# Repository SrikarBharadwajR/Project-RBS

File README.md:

# Project-RBS
A fully autonomous rubik's cube solving robot

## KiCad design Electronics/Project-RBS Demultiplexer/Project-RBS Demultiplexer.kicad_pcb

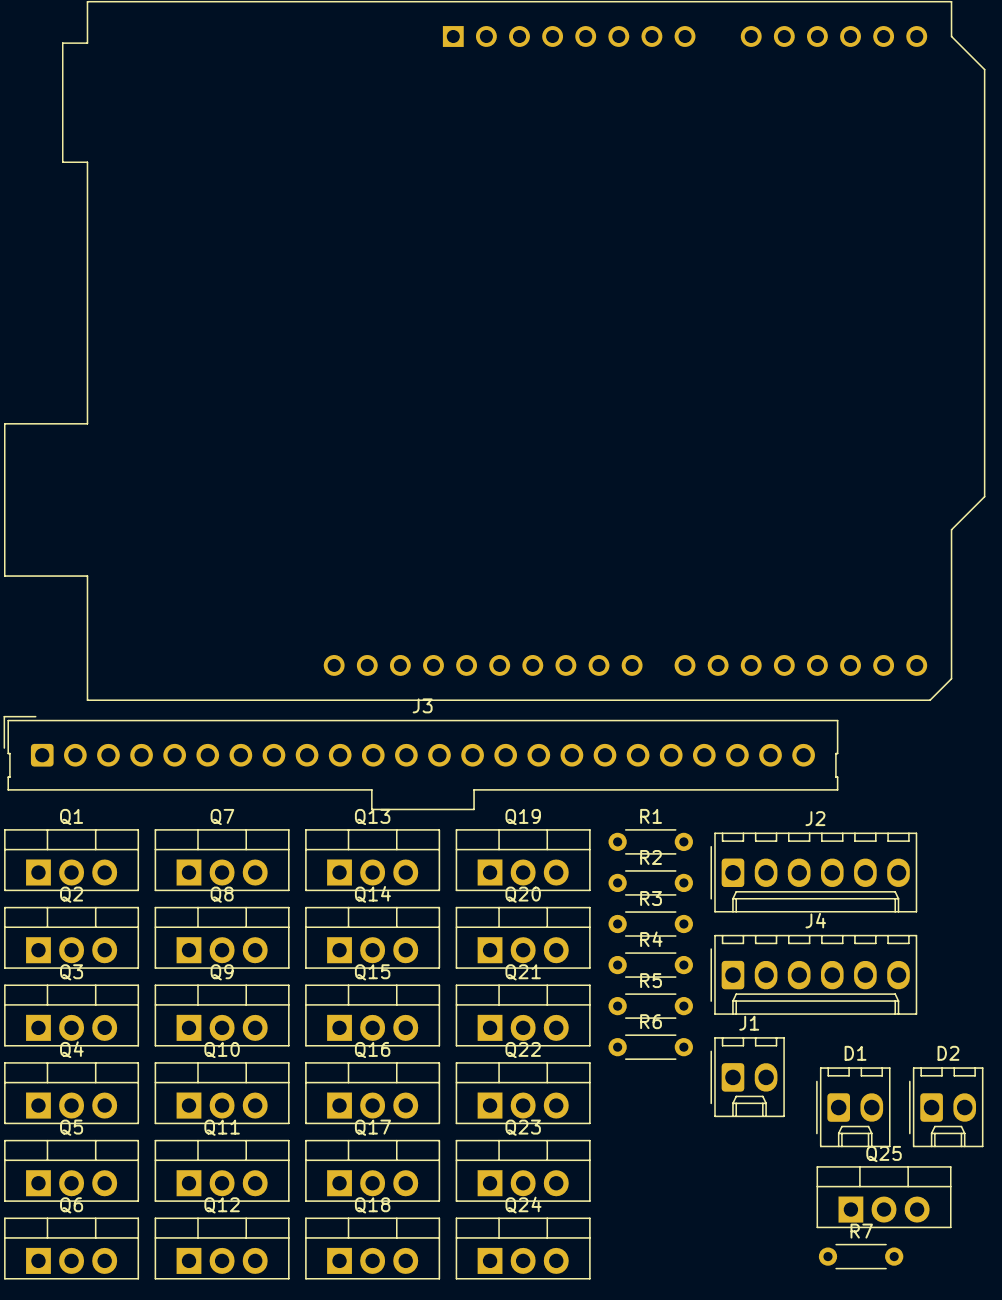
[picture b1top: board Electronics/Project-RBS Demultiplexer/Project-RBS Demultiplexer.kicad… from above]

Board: 2 copper layers, 39 parts (0 on the bottom side), 42 nets, no tracks yet.

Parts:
A1: Arduino_UNO_R3
D1, D2: LED; Molex_KK-254_AE-6410-02A_1x02_P2.54mm_Vertical
J1: Power Supply; Molex_KK-254_AE-6410-02A_1x02_P2.54mm_Vertical
J2, J4: TB6600; Molex_KK-254_AE-6410-06A_1x06_P2.54mm_Vertical
J3: OUTPUT; Molex_SL_171971-0024_1x24_P2.54mm_Vertical
Q1, Q2, Q3, Q4, Q5, Q6, Q7, Q8, Q9, Q10, Q11, Q12, Q13, Q14, Q15, Q16, Q17, Q18, Q19, Q20, Q21, Q22, Q23, Q24, Q25: IRFZ44N; TO-220-3_Vertical
R1, R2, R3, R4, R5, R6: 10k; R_Axial_DIN0204_L3.6mm_D1.6mm_P5.08mm_Horizontal
R7: 30; R_Axial_DIN0204_L3.6mm_D1.6mm_P5.08mm_Horizontal

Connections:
/5V: A1.5 (+5V), J2.2
/12V Vcc: J1.2, J4.6, R7.1
/A+: J4.4, Q1.3 (S), Q3.3 (S), Q9.3 (S), Q11.3 (S), Q17.3 (S), Q19.3 (S)
/A-: J4.3, Q2.3 (S), Q4.3 (S), Q10.3 (S), Q12.3 (S), Q18.3 (S), Q20.3 (S)
/B+: J4.2, Q5.3 (S), Q7.3 (S), Q13.3 (S), Q15.3 (S), Q21.3 (S), Q23.3 (S)
/B-: J4.1, Q6.3 (S), Q8.3 (S), Q14.3 (S), Q16.3 (S), Q22.3 (S), Q24.3 (S)
/D2: A1.17 (D2), Q1.1 (G), Q2.1 (G), Q5.1 (G), Q6.1 (G), R1.1
/D3: A1.18 (D3), Q3.1 (G), Q4.1 (G), Q7.1 (G), Q8.1 (G), R2.1
/D4: A1.19 (D4), Q9.1 (G), Q10.1 (G), Q13.1 (G), Q14.1 (G), R3.1
/D5: A1.20 (D5), Q11.1 (G), Q12.1 (G), Q15.1 (G), Q16.1 (G), R4.1
/D6: A1.21 (D6), Q17.1 (G), Q18.1 (G), Q21.1 (G), Q22.1 (G), R5.1
/D7: A1.22 (D7), Q19.1 (G), Q20.1 (G), Q23.1 (G), Q24.1 (G), R6.1
/D10: A1.25 (D10), Q25.1 (G)
/DIR: A1.23 (D8), J2.4
/GND: A1.6 (GND), A1.7 (GND), A1.29 (GND), D1.1 (K), D2.1 (K), J1.1, J2.1, J2.3, J2.5, J4.5, R1.2, R2.2, R3.2, R4.2, R5.2, R6.2
/M1 A+: J3.1, Q1.2 (D)
/M1 A-: J3.2, Q2.2 (D)
/M1 B+: J3.3, Q5.2 (D)
/M1 B-: J3.4, Q6.2 (D)
/M2 A+: J3.5, Q3.2 (D)
/M2 A-: J3.6, Q4.2 (D)
/M2 B+: J3.7, Q7.2 (D)
/M2 B-: J3.8, Q8.2 (D)
/M3 A+: J3.9, Q9.2 (D)
/M3 A-: J3.10, Q10.2 (D)
/M3 B+: J3.11, Q13.2 (D)
/M3 B-: J3.12, Q14.2 (D)
/M4 A+: J3.13, Q11.2 (D)
/M4 A-: J3.14, Q12.2 (D)
/M4 B+: J3.15, Q15.2 (D)
/M4 B-: J3.16, Q16.2 (D)
/M5 A+: J3.17, Q17.2 (D)
/M5 A-: J3.18, Q18.2 (D)
/M5 B+: J3.19, Q21.2 (D)
/M5 B-: J3.20, Q22.2 (D)
/M6 A+: J3.21, Q19.2 (D)
/M6 A-: J3.22, Q20.2 (D)
/M6 B+: J3.23, Q23.2 (D)
/M6 B-: J3.24, Q24.2 (D)
/PUL: A1.24 (D9), J2.6
unnamed: D1.2 (A), D2.2 (A), Q25.2 (D)
unnamed: Q25.3 (S), R7.2

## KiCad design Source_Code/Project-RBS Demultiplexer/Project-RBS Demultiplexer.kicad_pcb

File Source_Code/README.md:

# Project-RBS
- A Robot which can scan a scrambled 3x3 Rubik's cube, and generate the steps required to sovle it. 
- Those steps are uploaded to a MCU which actuates 6 stepper motors accordingly, which are coupled with a physical 3x3 Rubik's cube.
- Scanning process is done by OpenCV ROI and colour detection features, which are performed multiple times on a particular face of the cube logically to scan the scrambled configuration of the cube.

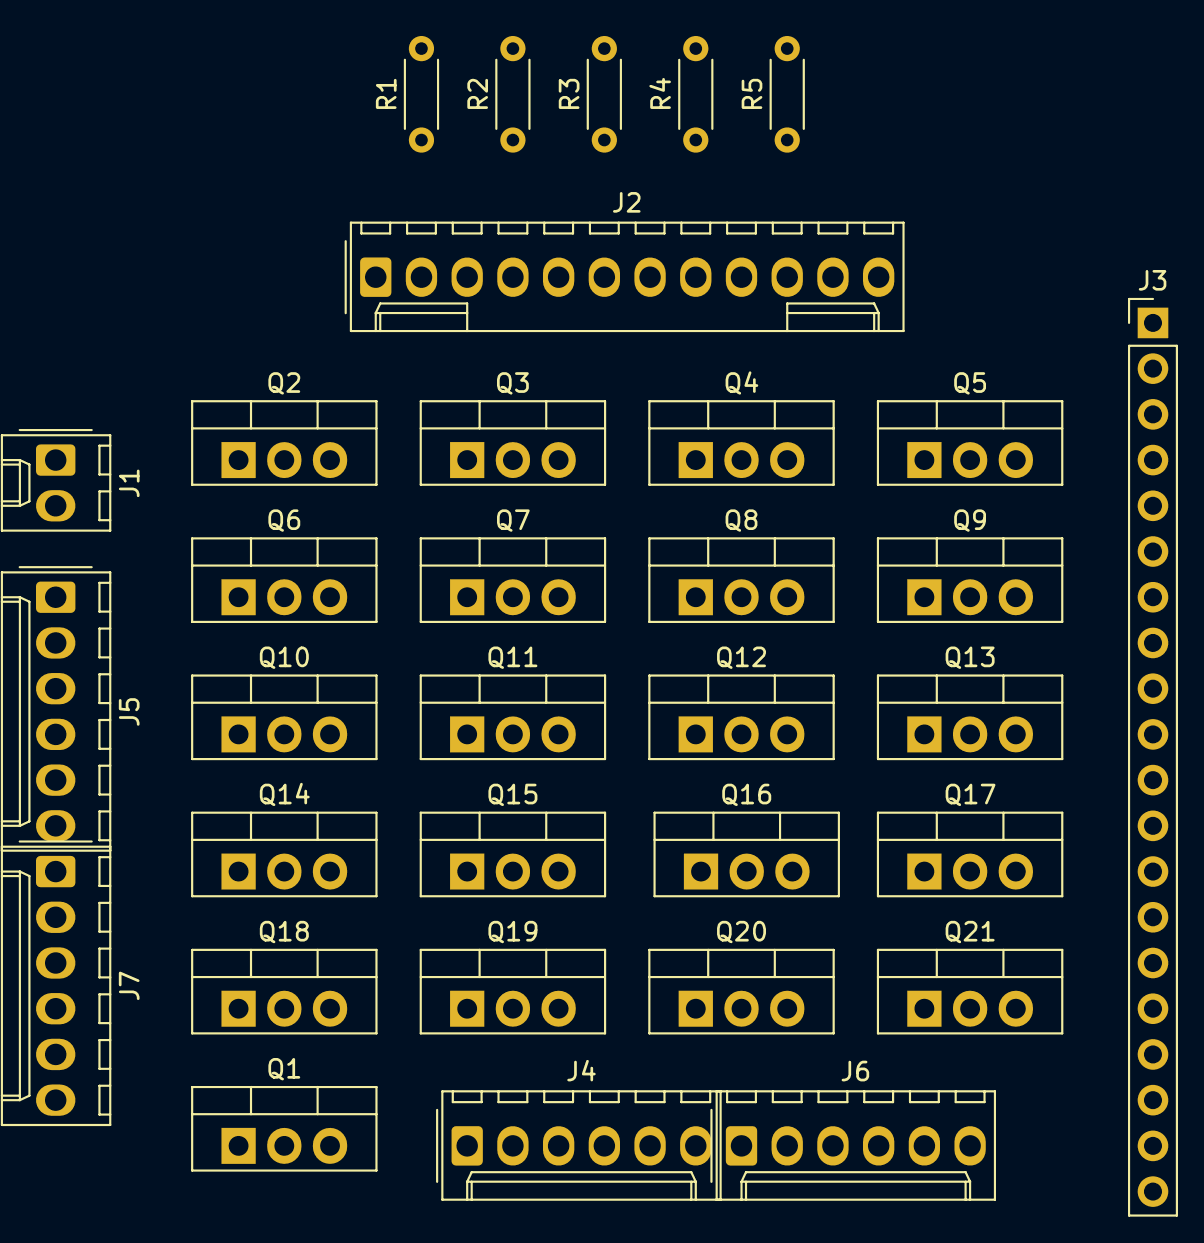
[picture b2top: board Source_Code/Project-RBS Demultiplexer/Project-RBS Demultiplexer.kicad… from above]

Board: 2 copper layers, 33 parts (0 on the bottom side), 41 nets, no tracks yet.

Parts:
J1: Power Supply; Molex_KK-254_AE-6410-02A_1x02_P2.54mm_Vertical
J2: Arduino_UNO_R3; Molex_KK-254_AE-6410-12A_1x12_P2.54mm_Vertical
J3: Stepper_Pins; PinHeader_1x20_P2.54mm_Vertical
J4, J5, J6, J7: TB6600; Molex_KK-254_AE-6410-06A_1x06_P2.54mm_Vertical
Q1, Q2, Q3, Q4, Q5, Q6, Q7, Q8, Q9, Q10, Q11, Q12, Q13, Q14, Q15, Q16, Q17, Q18, Q19, Q20, Q21: IRFZ44N; TO-220-3_Vertical
R1, R2, R3, R4, R5: 10k; R_Axial_DIN0204_L3.6mm_D1.6mm_P5.08mm_Horizontal

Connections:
/5V: J4.2, J5.2
/12V Vcc: J1.2, J6.6, J7.6
/A1+: J6.4, Q2.3 (S), Q4.3 (S), Q12.3 (S)
/A1-: J6.3, Q3.3 (S), Q5.3 (S), Q13.3 (S)
/A2+: J7.4, Q10.3 (S), Q18.3 (S)
/A2-: J7.3, Q11.3 (S), Q19.3 (S)
/B1+: J6.2, Q6.3 (S), Q8.3 (S), Q16.3 (S)
/B1-: J6.1, Q7.3 (S), Q9.3 (S), Q17.3 (S)
/B2+: J7.2, Q14.3 (S), Q20.3 (S)
/B2-: J7.1, Q15.3 (S), Q21.3 (S)
/D2: J2.1, Q2.1 (G), Q3.1 (G), Q6.1 (G), Q7.1 (G), R1.1
/D3: J2.2, Q4.1 (G), Q5.1 (G), Q8.1 (G), Q9.1 (G), R2.1
/D4: J2.3, Q10.1 (G), Q11.1 (G), Q14.1 (G), Q15.1 (G), R3.1
/D5: J2.4, Q12.1 (G), Q13.1 (G), Q16.1 (G), Q17.1 (G), R4.1
/D6: J2.5, Q18.1 (G), Q19.1 (G), Q20.1 (G), Q21.1 (G), R5.1
/D13: J2.12, Q1.1 (G)
/DIR_1: J2.6, J4.4
/DIR_2: J2.8, J5.4
/GND: J1.1, J4.1, J4.3, J4.5, J5.1, J5.3, J5.5, J6.5, J7.5, R1.2, R2.2, R3.2, R4.2, R5.2
/M1 A+: J3.1, Q2.2 (D)
/M1 A-: J3.2, Q3.2 (D)
/M1 B+: J3.3, Q6.2 (D)
/M1 B-: J3.4, Q7.2 (D)
/M2 A+: J3.5, Q4.2 (D)
/M2 A-: J3.6, Q5.2 (D)
/M2 B+: J3.7, Q8.2 (D)
/M2 B-: J3.8, Q9.2 (D)
/M3 A+: J3.9, Q10.2 (D)
/M3 A-: J3.10, Q11.2 (D)
/M3 B+: J3.11, Q14.2 (D)
/M3 B-: J3.12, Q15.2 (D)
/M4 A+: J3.13, Q12.2 (D)
/M4 A-: J3.14, Q13.2 (D)
/M4 B+: J3.15, Q16.2 (D)
/M4 B-: J3.16, Q17.2 (D)
/M5 A+: J3.17, Q18.2 (D)
/M5 A-: J3.18, Q19.2 (D)
/M5 B+: J3.19, Q20.2 (D)
/M5 B-: J3.20, Q21.2 (D)
/PUL_1: J2.7, J4.6
/PUL_2: J2.9, J5.6

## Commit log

2023-07-19 Project-RBS
